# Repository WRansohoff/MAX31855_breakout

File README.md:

# MAX31855 Thermocouple Amplifier Board

This is a simple breakout board for a `MAX31855` thermocouple amplifier. It is an easy-to-use chip which handles all of the fancy math and analog conversion for calculating the temperature output from a thermocouple.

Need to measure temperatures higher than a couple hundred degrees C? Give one of these a try.

See `max31855_BOM.csv` for a bill of materials, but the only oddly-sized part is the screw terminal block.

See `firmware/` for an example STM32 program which reads the currently detected temperature value out of the chip if one is connected.

# Board Renders:

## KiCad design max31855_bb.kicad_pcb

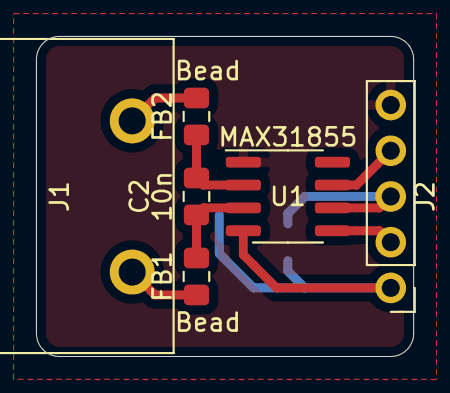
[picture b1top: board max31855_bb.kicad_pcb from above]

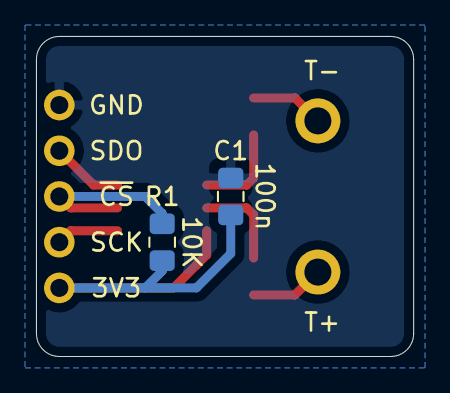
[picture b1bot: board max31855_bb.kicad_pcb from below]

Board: 2 copper layers, 21.0 x 17.8 mm, 8 parts (2 on the bottom side), 9 nets.

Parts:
C1: 100n; C_0805_2012Metric_Pad1.15x1.40mm_HandSolder
C2: 10n; C_0805_2012Metric_Pad1.15x1.40mm_HandSolder
FB1, FB2: Bead; R_0805_2012Metric_Pad1.15x1.40mm_HandSolder
J1: Therm; OSTYK42102030
J2: Breakout; PinHeader_1x05_P2.54mm_Vertical
R1: 10K; R_0805_2012Metric_Pad1.15x1.40mm_HandSolder
U1: MAX31855; SOIC-8_3.9x4.9mm_P1.27mm

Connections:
CK: J2.2, U1.5
DO: J2.4, U1.7
GND: C1.2, J2.5, U1.1
unnamed: C2.1, FB2.1, U1.2
unnamed: C2.2, FB1.1, U1.3
unnamed: FB1.2, J1.2
unnamed: FB2.2, J1.1
VCC: C1.1, J2.1, R1.1, U1.4
~CS: J2.3, R1.2, U1.6

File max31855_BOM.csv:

Part ID,Part type,Part size,Part value,Example Digikey Item,Cost
C1,Capacitor,0805,100nF,https://www.digikey.com/short/zz0pb1,$0.10
C2,Capacitor,0805,10nF,https://www.digikey.com/short/zz0p5q,$0.10
"FB1, FB2",Ferrite Bead,0805,Generic Filtering,https://www.digikey.com/short/zz0p59,$0.20
J1,Screw Terminal,"3/8""",1x2,https://www.digikey.com/short/zz0pb2,$0.83
R1,Resistor,0805,10KΩ,https://www.digikey.com/short/zz0p5f,$0.10
U1,Thermocouple Amplifier,SOIC-8,MAX31855,https://www.digikey.com/short/zz0pmp,$5.31
Total,-,-,-,-,$6.64

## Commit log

2020-05-05 Add the initial KiCAD project
2020-05-06 Add a license and readme
2020-05-06 Add a bill of materials
2020-05-06 Add supporting firmware files
2020-05-06 Add test program demonstrating how to read temperature data from the chip.
2020-05-06 Don't configure the MOSI pin; it isn't used
2020-05-06 Add PCB renders
